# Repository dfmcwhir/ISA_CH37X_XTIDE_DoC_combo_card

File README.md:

# ISA_CH37X_XTIDE_DoC_combo_card
ISA card with a CH375/CH376 Chip or module, XTIDE ROM chip, and a Disk on Chip module.

I designed this card for my personal use with the intended purpose of being able to use it to be able to quickly boot-up, setup and/or troubleshoot older 8088-386 DOS computers. I have been using this card for awhile and I like it. I'm posting this here in case anybody else wants to try it or experiment with it. I'm not a professional anything so there my be hardware, firmware, and/or SW bugs.

<b>Parts:</b>
  - The pcb can be obtained from PCBway here:
<a href="https://www.pcbway.com/project/shareproject/ISA_Card_with_XTIDE_ROM_Disk_on_Chip_USB_8e0c1eca.html">https://www.pcbway.com/project/shareproject/ISA_Card_with_XTIDE_ROM_Disk_on_Chip_USB_8e0c1eca.html</a>
or whatever pcb supplier you choose.
  - The DoC module is obsolete but can be found on ebay.
  - The Ch375 or Ch376 can be found on Aliexpress

<br><br>

<b>SW1:</b>
- SW1.1 ON = Disables USB hardware. Not currently implemented, see Known Issues
- SW1.2 ON = Disables the DoC module. This can be useful if you don't want it to boot from the DoC or because of an address conflict
- SW1.3 ON = Disables the XTIDE ROM. This can be useful on a system that doesn't need the XTIDE ROM and/or to avoid an address conflict

<br>
<b>Addr Sel jumpers:</b>
The Addr Sel jumpers can set the address of the XTIDE ROM and DoC to one of a few different values listed below. The specific addresses could be reprogrammed in the DOC_ROM_DEC pld.<br>
  - ROM#1 - OFF, ROM#2 - OFF --> ROM address = C0000h<br>
  - ROM#1 - ON, ROM#2 - OFF --> ROM address = C8000h<br>
  - ROM#1 - OFF, ROM#2 - ON --> ROM address = D0000h<br> 
  - ROM#1 - ON, ROM#2 - ON --> ROM address = D8000h<br>
  - DOC#1 - OFF, DOC#2 - OFF --> DOC address = C0000h<br>
  - DOC#1 - ON, DOC#2 - OFF --> DOC address = C8000h<br>
  - DOC#1 - OFF, DOC#2 - ON --> DOC address = D0000h<br>
  - DOC#1 - ON, DOC#2 - ON --> DOC address = D8000h<br>
<br>

<b>CH375 or CH376:</b>
There are two options for the USB port support that have been tested <br>
OPTION #1 - Install a CH375A or B SMT chip and all the supporting components (U3, Y1, J3, R3, C1, C2, C3, C4, C6, C8) <br>
OR <br>
OPTION #2 - Don't install any of the components above and instead install the 2x8 female header J4 and then use CH376 module such as https://www.aliexpress.us/item/3256807155423379.html. Double check the pinout of whatever module you buy to make sure it matches the labels on the card, keeping in mind the module is intended to be plugged in upside (component side) down. <br>
<br>
It is probable that a CH376 chip could be installed instead of the CH376 in option #1 or a CH375 module could be used instead of the CH376 module in option #2 if you can one with the correct pinout. This hasn't bee tested. <br>
<br>
<b>Known issues:</b><br>
  * Rev0 of this card had a defect where the MEMr and MEMw lines were swapped at the ISA connected. The card worked after bodging those connections. This was fixed in Rev1, which is what is uploaded here, so this USED to be an issue but should be fine now.
  * The USB disable switch is connected, but not implemented in the USB address decoding PLD yet, so it doesn't actually disable anything.
  * The USB address is hard coded as 0260h in the PLD, it can be changed by requires re-programming that chip.
  * The XTIDE has to be a 27256 chip. It is possible a 2764, 27128, 28256, etc could be used but you would have to check the datasheets/pinouts and bodge as necessary. Specifically, I think if a smaller chip is used, the VPP needs to be tied high, but you would have to double check.
  * The Disk on Chip module is specifically the M-Systems MD-2800-D08 chip. I'm not sure if other versions of this chip will work. Specifically, there is a chip that ends with something like -3V that is a 3V version of the chip and won't work.
  * The initial formatting of the DoC module was a challenge for me. At least on my system, the DoC was always detected first amd the computer would try to boot from it first, but if it isn't formatted yet, then it will fail. But if you boot it with the DoC disabled with the switch, then even after re-enabling it, the DoC software wouldn't detect the card. My solution was the slightly risking procedure of booting with the DoC disabled then after booting, re-moving the card, flipping the disable switch off, then re-installing the card with while the computer was still powered up. If I did that, then the DoC software would see the module and let me format it. All of this may have been complicated by quirks of my system, like I needed this card installed at boot because I needed the XTIDE ROM installed to be able to boot at all.
  * There are several options for a DOS driver for the CH375 chip, but if a CH376 is used, I was unable to find one. Eventually I was able to get AI to make a driver for the CH376. That driver is here: https://github.com/dfmcwhir/CH376DOS_driver
  * Regardless of which driver is used, this card has only been tested with the interrupt option on the driver set to 0 (disabled). To be honest there is part of the HW for this card that was copied from the original CH375 reference design that I don't understand. The PLD has the ability to make it so the INT from the CH375 can be read from the base address + 2 and it will be on D0. I don't know if with the CH735 stock driver it uses that port all the time, or if it uses it when the interrupt option on the driver is set to something other than 0, or ???. There is also another version of the CH375 reference board that specifically says it an interrupt version of the board, so maybe the driver interrupt value is only for that card? I know that my CH376 driver never uses that base address + 2 port, so I assume it will only work with the interrupt option set to 0.
  * The form factor of the board doesn't match ISA specifications in terms of offset from the rear of the MB and mounting hole spacing. This was done as a cost saving measure to keep the board size < 100mm x 100mm. The result of that is the USB port maybe hard to plug thing into through the gaps in the card bracket on the computer.
<br><br>

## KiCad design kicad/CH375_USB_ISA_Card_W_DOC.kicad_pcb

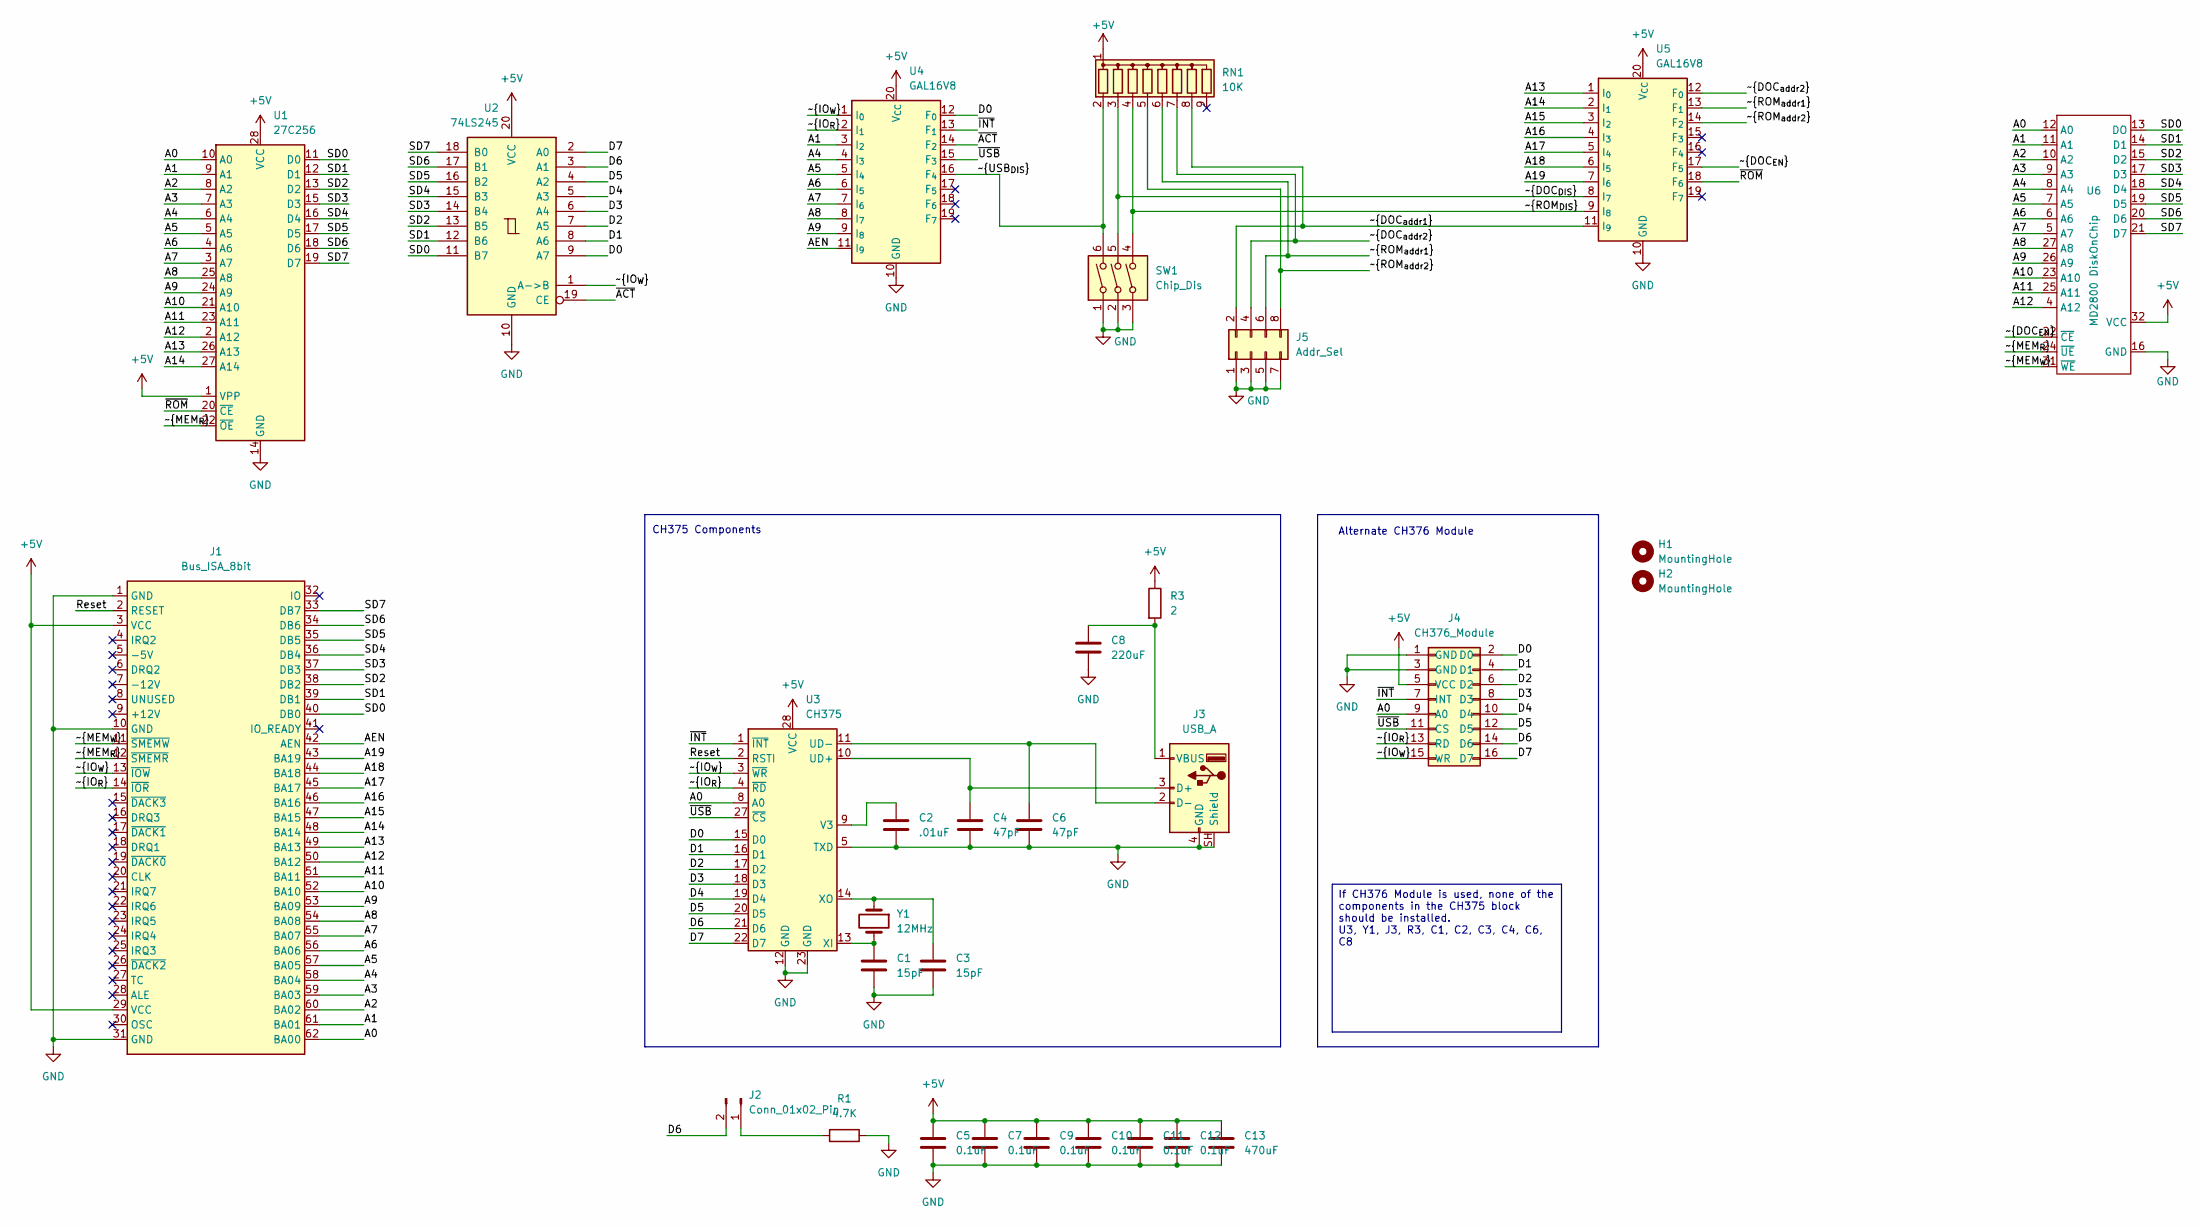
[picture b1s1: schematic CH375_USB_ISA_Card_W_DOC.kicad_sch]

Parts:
C1, C3: 15pF; C_Disc_D4.7mm_W2.5mm_P5.00mm
C2: .01uF; C_Disc_D4.7mm_W2.5mm_P5.00mm
C4, C6: 47pF; C_Disc_D4.7mm_W2.5mm_P5.00mm
C5, C7, C9, C10, C11, C12: 0.1uF; C_Disc_D4.7mm_W2.5mm_P5.00mm
C8: 220uF; CP_Radial_D6.3mm_P2.50mm
C13: 470uF; CP_Radial_D6.3mm_P2.50mm
H1, H2: MountingHole; MountingHole_3.2mm_M3
J1: Bus_ISA_8bit; BUS_8-bit_ISA
J2: Conn_01x02_Pin; PinHeader_1x02_P2.54mm_Vertical
J3: USB_A; USB_A_Connfly_DS1095
J4: CH376_Module
J5: Addr_Sel; PinHeader_2x04_P2.54mm_Vertical
R1: 4.7K; R_Axial_DIN0207_L6.3mm_D2.5mm_P10.16mm_Horizontal
R3: 2; R_Axial_DIN0207_L6.3mm_D2.5mm_P10.16mm_Horizontal
RN1: 10K; R_Array_SIP9
SW1: Chip_Dis; DIP-6_W7.62mm
U1: 27C256; DIP-28_W15.24mm
U2: 74LS245; DIP-20_W7.62mm
U3: CH375; SOP-28_8.4x18.16mm_P1.27mm
U4, U5: GAL16V8; DIP-20_W7.62mm
U6: MD2800 DiskOnChip; DIP-32_W15.24mm
Y1: 12MHz; Crystal_HC18-U_Vertical

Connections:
+5V: C5.1, C7.1, C9.1, C10.1, C11.1, C12.1, C13.1, J1.3 (VCC), J1.29 (VCC), J4.5 (VCC), R3.1, RN1.1 (common), U1.1 (VPP), U1.28 (VCC), U2.20 (VCC), U3.28 (VCC), U4.20 (V_{CC}), U5.20 (V_{CC}), U6.32 (VCC)
/A0: J1.62 (BA00), J4.9 (A0), U1.10 (A0), U3.8 (A0), U6.12 (A0)
/A1: J1.61 (BA01), U1.9 (A1), U4.3 (I_{2}), U6.11 (A1)
/A2: J1.60 (BA02), U1.8 (A2), U6.10 (A2)
/A3: J1.59 (BA03), U1.7 (A3), U6.9 (A3)
/A4: J1.58 (BA04), U1.6 (A4), U4.4 (I_{3}), U6.8 (A4)
/A5: J1.57 (BA05), U1.5 (A5), U4.5 (I_{4}), U6.7 (A5)
/A6: J1.56 (BA06), U1.4 (A6), U4.6 (I_{5}), U6.6 (A6)
/A7: J1.55 (BA07), U1.3 (A7), U4.7 (I_{6}), U6.5 (A7)
/A8: J1.54 (BA08), U1.25 (A8), U4.8 (I_{7}), U6.27 (A8)
/A9: J1.53 (BA09), U1.24 (A9), U4.9 (I_{8}), U6.26 (A9)
/A10: J1.52 (BA10), U1.21 (A10), U6.23 (A10)
/A11: J1.51 (BA11), U1.23 (A11), U6.25 (A11)
/A12: J1.50 (BA12), U1.2 (A12), U6.4 (A12)
/A13: J1.49 (BA13), U1.26 (A13), U5.1 (I_{0})
/A14: J1.48 (BA14), U1.27 (A14), U5.2 (I_{1})
/A15: J1.47 (BA15), U5.3 (I_{2})
/A16: J1.46 (BA16), U5.4 (I_{3})
/A17: J1.45 (BA17), U5.5 (I_{4})
/A18: J1.44 (BA18), U5.6 (I_{5})
/A19: J1.43 (BA19), U5.7 (I_{6})
/AEN: J1.42 (AEN), U4.11 (I_{9})
/D0: J4.2 (D0), U2.9 (A7), U3.15 (D0), U4.12 (F_{0})
/D1: J4.4 (D1), U2.8 (A6), U3.16 (D1)
/D2: J4.6 (D2), U2.7 (A5), U3.17 (D2)
/D3: J4.8 (D3), U2.6 (A4), U3.18 (D3)
/D4: J4.10 (D4), U2.5 (A3), U3.19 (D4)
/D5: J4.12 (D5), U2.4 (A2), U3.20 (D5)
/D6: J2.2, J4.14 (D6), U2.3 (A1), U3.21 (D6)
/D7: J4.16 (D7), U2.2 (A0), U3.22 (D7)
/Reset: J1.2 (RESET), U3.2 (RSTI)
/SD0: J1.40 (DB0), U1.11 (D0), U2.11 (B7), U6.13 (DO)
/SD1: J1.39 (DB1), U1.12 (D1), U2.12 (B6), U6.14 (D1)
/SD2: J1.38 (DB2), U1.13 (D2), U2.13 (B5), U6.15 (D2)
/SD3: J1.37 (DB3), U1.15 (D3), U2.14 (B4), U6.17 (D3)
/SD4: J1.36 (DB4), U1.16 (D4), U2.15 (B3), U6.18 (D4)
/SD5: J1.35 (DB5), U1.17 (D5), U2.16 (B2), U6.19 (D5)
/SD6: J1.34 (DB6), U1.18 (D6), U2.17 (B1), U6.20 (D6)
/SD7: J1.33 (DB7), U1.19 (D7), U2.18 (B0), U6.21 (D7)
/~ACT: U2.19 (CE), U4.14 (F_{2})
/~DOC_{DIS}: RN1.3 (R2), SW1.5, U5.8 (I_{7})
/~DOC_{EN}: U5.17 (F_{5}), U6.22 (~CE)
/~DOC_{addr1}: J5.2, RN1.8 (R7), U5.11 (I_{9})
/~DOC_{addr2}: J5.4, RN1.7 (R6), U5.12 (F_{0})
/~INT: J4.7 (INT), U3.1 (~INT), U4.13 (F_{1})
/~IO_{R}: J1.14 (~IOR), J4.13 (RD), U3.4 (~RD), U4.2 (I_{1})
/~IO_{W}: J1.13 (~IOW), J4.15 (WR), U2.1 (A->B), U3.3 (~WR), U4.1 (I_{0})
/~MEM_{R}: J1.12 (~SMEMR), U1.22 (~OE), U6.24 (~UE)
/~MEM_{W}: J1.11 (~SMEMW), U6.31 (~WE)
/~ROM_{DIS}: RN1.4 (R3), SW1.4, U5.9 (I_{8})
/~ROM_{addr1}: J5.6, RN1.6 (R5), U5.13 (F_{1})
/~ROM_{addr2}: J5.8, RN1.5 (R4), U5.14 (F_{2})
/~ROM: U1.20 (~CE), U5.18 (F_{6})
/~USB_{DIS}: RN1.2 (R1), SW1.6, U4.16 (F_{4})
/~USB: J4.11 (CS), U3.27 (~CS), U4.15 (F_{3})
GND: C1.2, C2.2, C3.2, C4.2, C5.2, C6.2, C7.2, C8.2, C9.2, C10.2, C11.2, C12.2, C13.2, J1.1 (GND), J1.10 (GND), J1.31 (GND), J3.4 (GND), J3.SH (Shield), J4.1 (GND), J4.3 (GND), J5.1, J5.3, J5.5, J5.7, R1.1, SW1.1, SW1.2, SW1.3, U1.14 (GND), U2.10 (GND), U3.5 (TXD), U3.12 (GND), U3.23 (GND), U4.10 (GND), U5.10 (GND), U6.16 (GND)
unnamed: J2.1, R1.2
unnamed: C4.1, J3.3 (D+), U3.10 (UD+)
unnamed: C6.1, J3.2 (D-), U3.11 (UD-)
unnamed: C8.1, J3.1 (VBUS), R3.2
unnamed: C2.1, U3.9 (V3)
unnamed: C1.1, U3.13 (XI), Y1.2
unnamed: C3.1, U3.14 (XO), Y1.1

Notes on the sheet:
CH375 Components
Alternate CH376 Module
If CH376 Module is used, none of the components in the CH375 block should be installed. U3, Y1, J3, R3, C1, C2, C3, C4, C6, C8

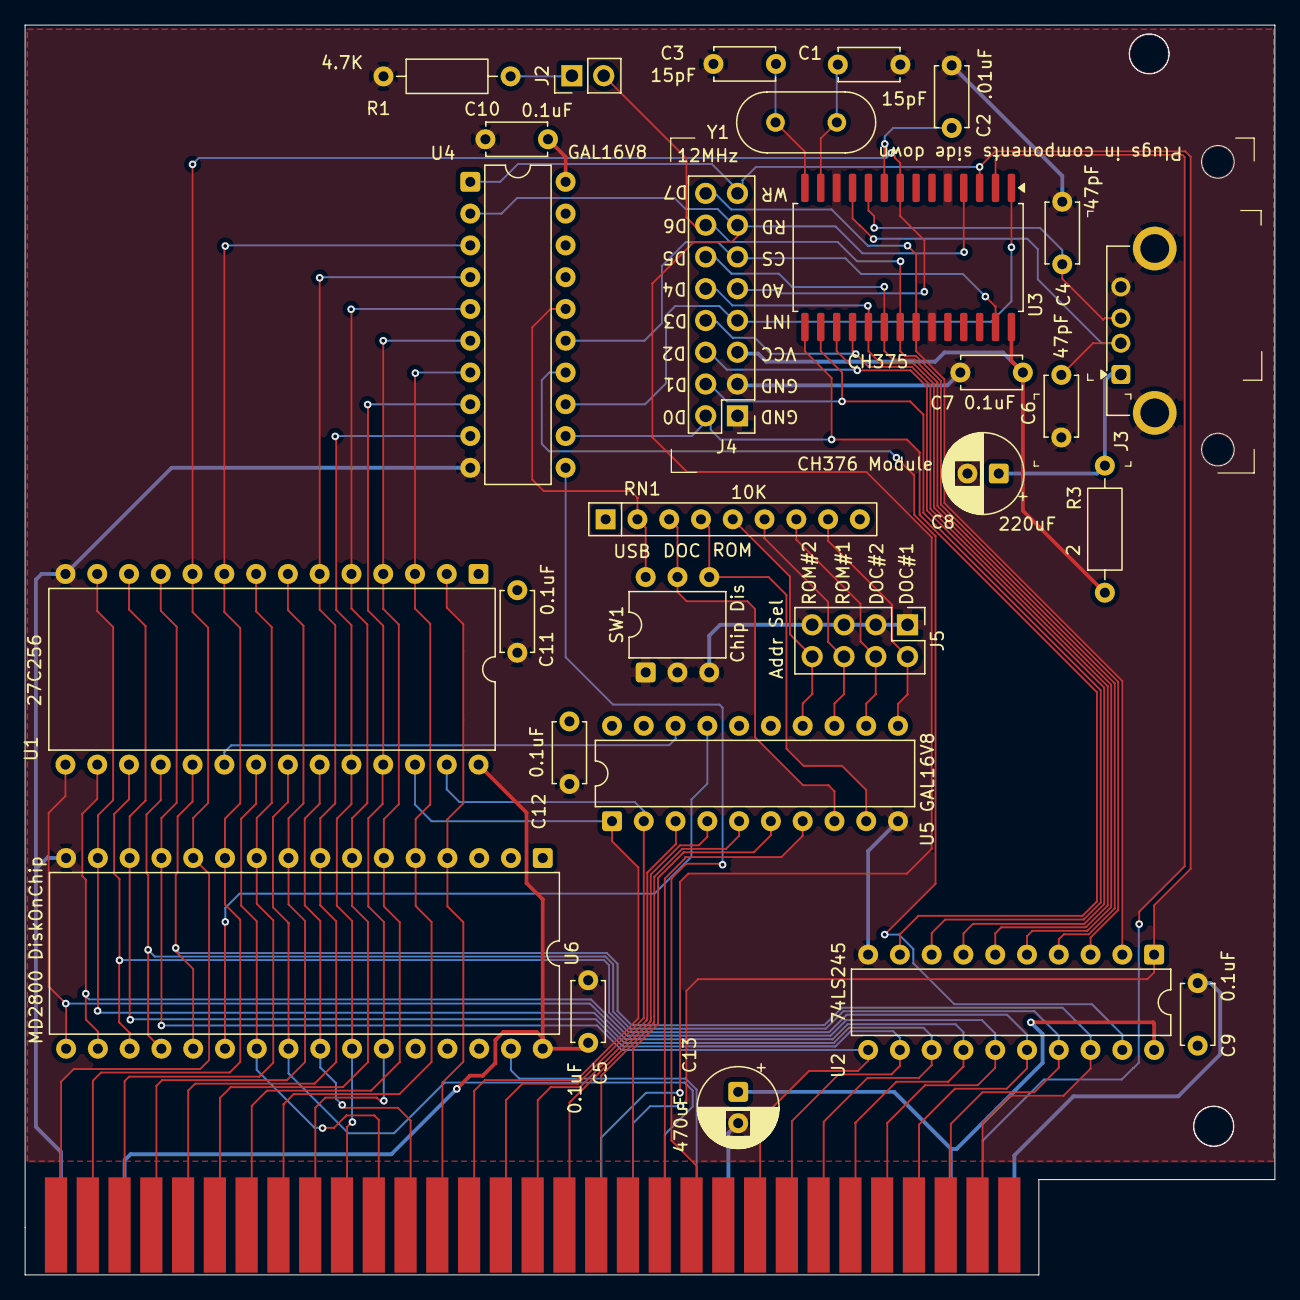
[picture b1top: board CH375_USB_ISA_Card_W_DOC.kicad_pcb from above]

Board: 2 copper layers, 99.9 x 99.9 mm, 29 parts (0 on the bottom side), 63 nets.
